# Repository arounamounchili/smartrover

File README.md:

# SmartRover

SmartRover is a teleoperated 4WD mobile robot built on the **ESP32-S3** in `no_std` asynchronous Rust (`embassy` + `esp-hal`). The repository includes the firmware, an embedded single-file web cockpit, KiCad PCB/manufacturing files, and parametric `build123d` mechanical models.

## Overview

- **Drive & Camera:** Differential 4WD skid-steer (4× A3908EEETR-T H-bridges on `MCPWM0` in paired left/right banks, no wheel encoders) + SPI Arducam OV5642 MJPEG stream on Core 1.
- **Browser Teleoperation:** Web Gamepad API (PlayStation, Xbox, and standard controllers), `WASD`/arrow keys, and touch/mouse X/Y pad.
- **Onboard Safety Supervision:**
  - **Obstacle Assist (VL53L0X):** 3-sample median-filtered ranging scales forward throttle below 320 mm, latches forward stop at <= 140 mm (165 mm release hysteresis; reverse and pivot steering remain allowed), and filters invalid or weak signal returns to ignore grazing floor reflections.
  - **Tilt & Free-Fall (BMI323):** Latches motor cutoff past 0.68 g for 400 ms or on free-fall; recovers once upright with neutral sticks.
  - **Watchdog & Battery (`ADC1`):** Cuts drive output after 600 ms without a control packet or below 15% battery (20% hysteresis).

## Project Structure

- [`src/`](src/) — ESP32-S3 firmware (`domain/` control & safety logic, `adapters/` tasks & shared state, `drivers/` for MCPWM0, BMI323, VL53L0X, OV5642, and ADC1, `camera/` Core 1 capture, `network/` Wi-Fi/DHCP/HTTP/MJPEG server).
- [`dashboard/`](dashboard/) — Single-file web cockpit (`dashboard.html.gz`) embedded into firmware flash.
- [`hardware/`](hardware/) — KiCad schematics, 4-layer PCB (45 × 80 mm), and [`hardware/manufacturing/`](hardware/manufacturing/) fabrication files (BOM, Gerbers, pick-and-place).
- [`mechanical/`](mechanical/) & [`3d-printing/`](3d-printing/) — Parametric `build123d` CAD sources and support-free printable STEP/STL files (62.0 × 115.5 mm unibody chassis).

## Controls

| Function | Gamepad | Keyboard | Touch / Mouse |
| :--- | :--- | :--- | :--- |
| **Throttle** | Left Stick Y or R2 / L2 Triggers | `W` / `S` or `Up` / `Down` | Drag pad vertically |
| **Steering** | Left Stick X or Right Stick X | `A` / `D` or `Left` / `Right` | Drag pad horizontally |
| **Speed Gear** | `LB` / `RB` (`L1` / `R1`) | `1`, `2`, `3` | Click Crawl / Normal / Sport |
| **Brake** | `B` (Circle) | `Space` | Hold Brake button |
| **Obstacle Assist** | `Y` (Triangle) | — | Click Assist button |

## Pinout (ESP32-S3-MINI-1)

| Subsystem | GPIO | Peripheral | Notes |
| :--- | :---: | :---: | :--- |
| **I2C Bus** | `8` (SDA), `9` (SCL) | `I2C0` | 400 kHz (BMI323, VL53L0X, OV5642) |
| **Camera SPI** | `34` (CS), `35` (MOSI), `36` (SCK), `37` (MISO) | `SPI2` | 8 MHz FIFO burst read on Core 1 |
| **Motors** | `11`, `12` (Left), `13`, `14` (Right) | `MCPWM0` | 16 kHz PWM to A3908 H-bridges |
| **Battery Sense** | `1` | `ADC1` | 2:1 voltage divider (3.3 V to 4.2 V) |
| **Status LEDs** | `3`, `4`, `5`, `6` | `GPIO` | Front White (`3`, `4`), Rear Red (`5`, `6`) state, ADAS, and fault indicators |

## Building and Testing

### Prerequisites
- **Rust (`esp` toolchain):** `channel = "esp"` ([`rust-toolchain.toml`](rust-toolchain.toml)) targeting `xtensa-esp32s3-none-elf` via `espup`, plus `espflash`.
- **Node.js & npm:** For `dashboard/` tests and asset bundling (`dashboard/dashboard.html.gz`).
- **`uv` *(optional, CAD only)*:** For verifying or regenerating 3D models in [`mechanical/`](mechanical/README.md).

### Test, Build & CAD Commands

```bash
# Run Rust host unit tests + dashboard unit tests (no ESP32-S3 required)
make test

# Run the full local CI suite (fmt, tests, dashboard bundle check, clippy, ESP32-S3 builds)
make ci

# Rebuild dashboard/dashboard.html.gz after editing dashboard/ (or `cd dashboard && npm run dev`)
make dashboard

# Verify clearances & regenerate STLs/STEPs in 3d-printing/
make cad-verify && make cad-export
```

### Flash to ESP32-S3

Connect a 3.3 V USB-UART bridge to `J201` (onboard USB-C is power-only), switch battery power **ON**, and enter download mode (**hold `BOOT`, press `RESET`, release `BOOT`**):

```bash
# Default SoftAP mode (SmartRover_AP / smartrover123 -> http://192.168.4.1/)
make dashboard && make flash PORT=/dev/cu.usbserial-0001

# Station (STA) mode (joins 2.4 GHz Wi-Fi; compile-time when WIFI_SSID is set)
make flash-sta WIFI_SSID="Your_2.4GHz_SSID" WIFI_PASS="Your_Password" PORT=/dev/cu.usbserial-0001
```

- **Port & baud overrides:** Omit `PORT=...` to auto-select, or override defaults (`--before no-reset -B 115200`) with `FLASH_BEFORE=default-reset BAUD=460800`.
- **Wi-Fi mode:** Selected at compile time via `WIFI_SSID`. In STA mode, the rover retries every 5 s without falling back to SoftAP and prints its assigned cockpit URL on serial (`Rover Cockpit: http://<ip>/`).

See [`mechanical/README.md`](mechanical/README.md) and [`3d-printing/README.md`](3d-printing/README.md) for CAD and printing details.

## HTTP API

| Endpoint | Description |
| :--- | :--- |
| `GET /` | Serves the gzip-compressed web cockpit (`dashboard.html.gz`). |
| `POST /control?t=&s=&g=&b=&a=` | Updates throttle/steering (`-1000..=1000`), gear (`1..=3`), brake (`0`/`1`), and obstacle assist (`0`/`1`); returns status JSON. |
| `GET /status` | Returns telemetry JSON (`dist`, `batt`, `state`, `adas_active`, `left_pwm`, `right_pwm`, `rssi`, `tof_ok`, `imu_ok`). |
| `GET /stream` | Multipart MJPEG camera stream (`multipart/x-mixed-replace; boundary=frame`; single active viewer, new connections preempt older ones). |

## License

MIT License. See [LICENSE](LICENSE).

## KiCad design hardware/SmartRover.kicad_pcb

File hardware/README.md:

# SmartRover Hardware & PCB

4-layer 1.6 mm FR4 carrier board (45 × 80 mm) designed in **KiCad 9.0+**.

- **Schematics (PDF):** [`schematics.pdf`](schematics.pdf)
- **KiCad Project:** [`SmartRover.kicad_pro`](SmartRover.kicad_pro), [`SmartRover.kicad_pcb`](SmartRover.kicad_pcb), and [`SmartRover.kicad_sch`](SmartRover.kicad_sch) linking:
  - [`PowerSupply.kicad_sch`](PowerSupply.kicad_sch) — MCP73833 LiPo charger (`IC101`), MP2153 3.3 V buck (`IC102`), USB-C power input (`J101`), JST-PH battery (`J102`), SPDT charge/run switch (`S101`).
  - [`Microcontroller.kicad_sch`](Microcontroller.kicad_sch) — ESP32-S3-MINI-1-N8 (`U201`), UART header (`J201`), Tag-Connect JTAG (`J202`), RESET/BOOT buttons (`S201`/`S202`), status LEDs.
  - [`SensorActuator.kicad_sch`](SensorActuator.kicad_sch) — 4× A3908 motor drivers (`IC301–IC304`), BMI323 IMU (`IC305`), Arducam header (`J309`), JST-SH I2C/ToF header (`J310`).
- **Manufacturing:** [`manufacturing/`](manufacturing/) (`BOM.csv`, `Gerbers.zip`, `Position-file.csv`).

All symbols and footprints are embedded inside the schematic and PCB files, so you can inspect the design and re-export fabrication outputs in KiCad 9.0+ without external libraries. (Custom third-party libraries referenced in [`sym-lib-table`](sym-lib-table) / [`fp-lib-table`](fp-lib-table) are only needed if you update symbols/footprints from libraries.)

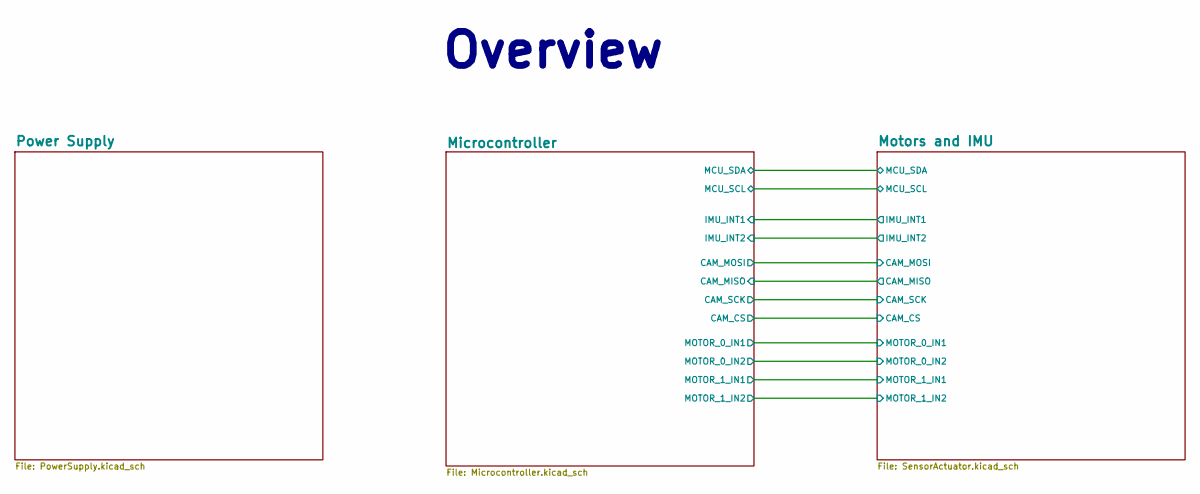
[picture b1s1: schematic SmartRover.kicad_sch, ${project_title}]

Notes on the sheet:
Overview

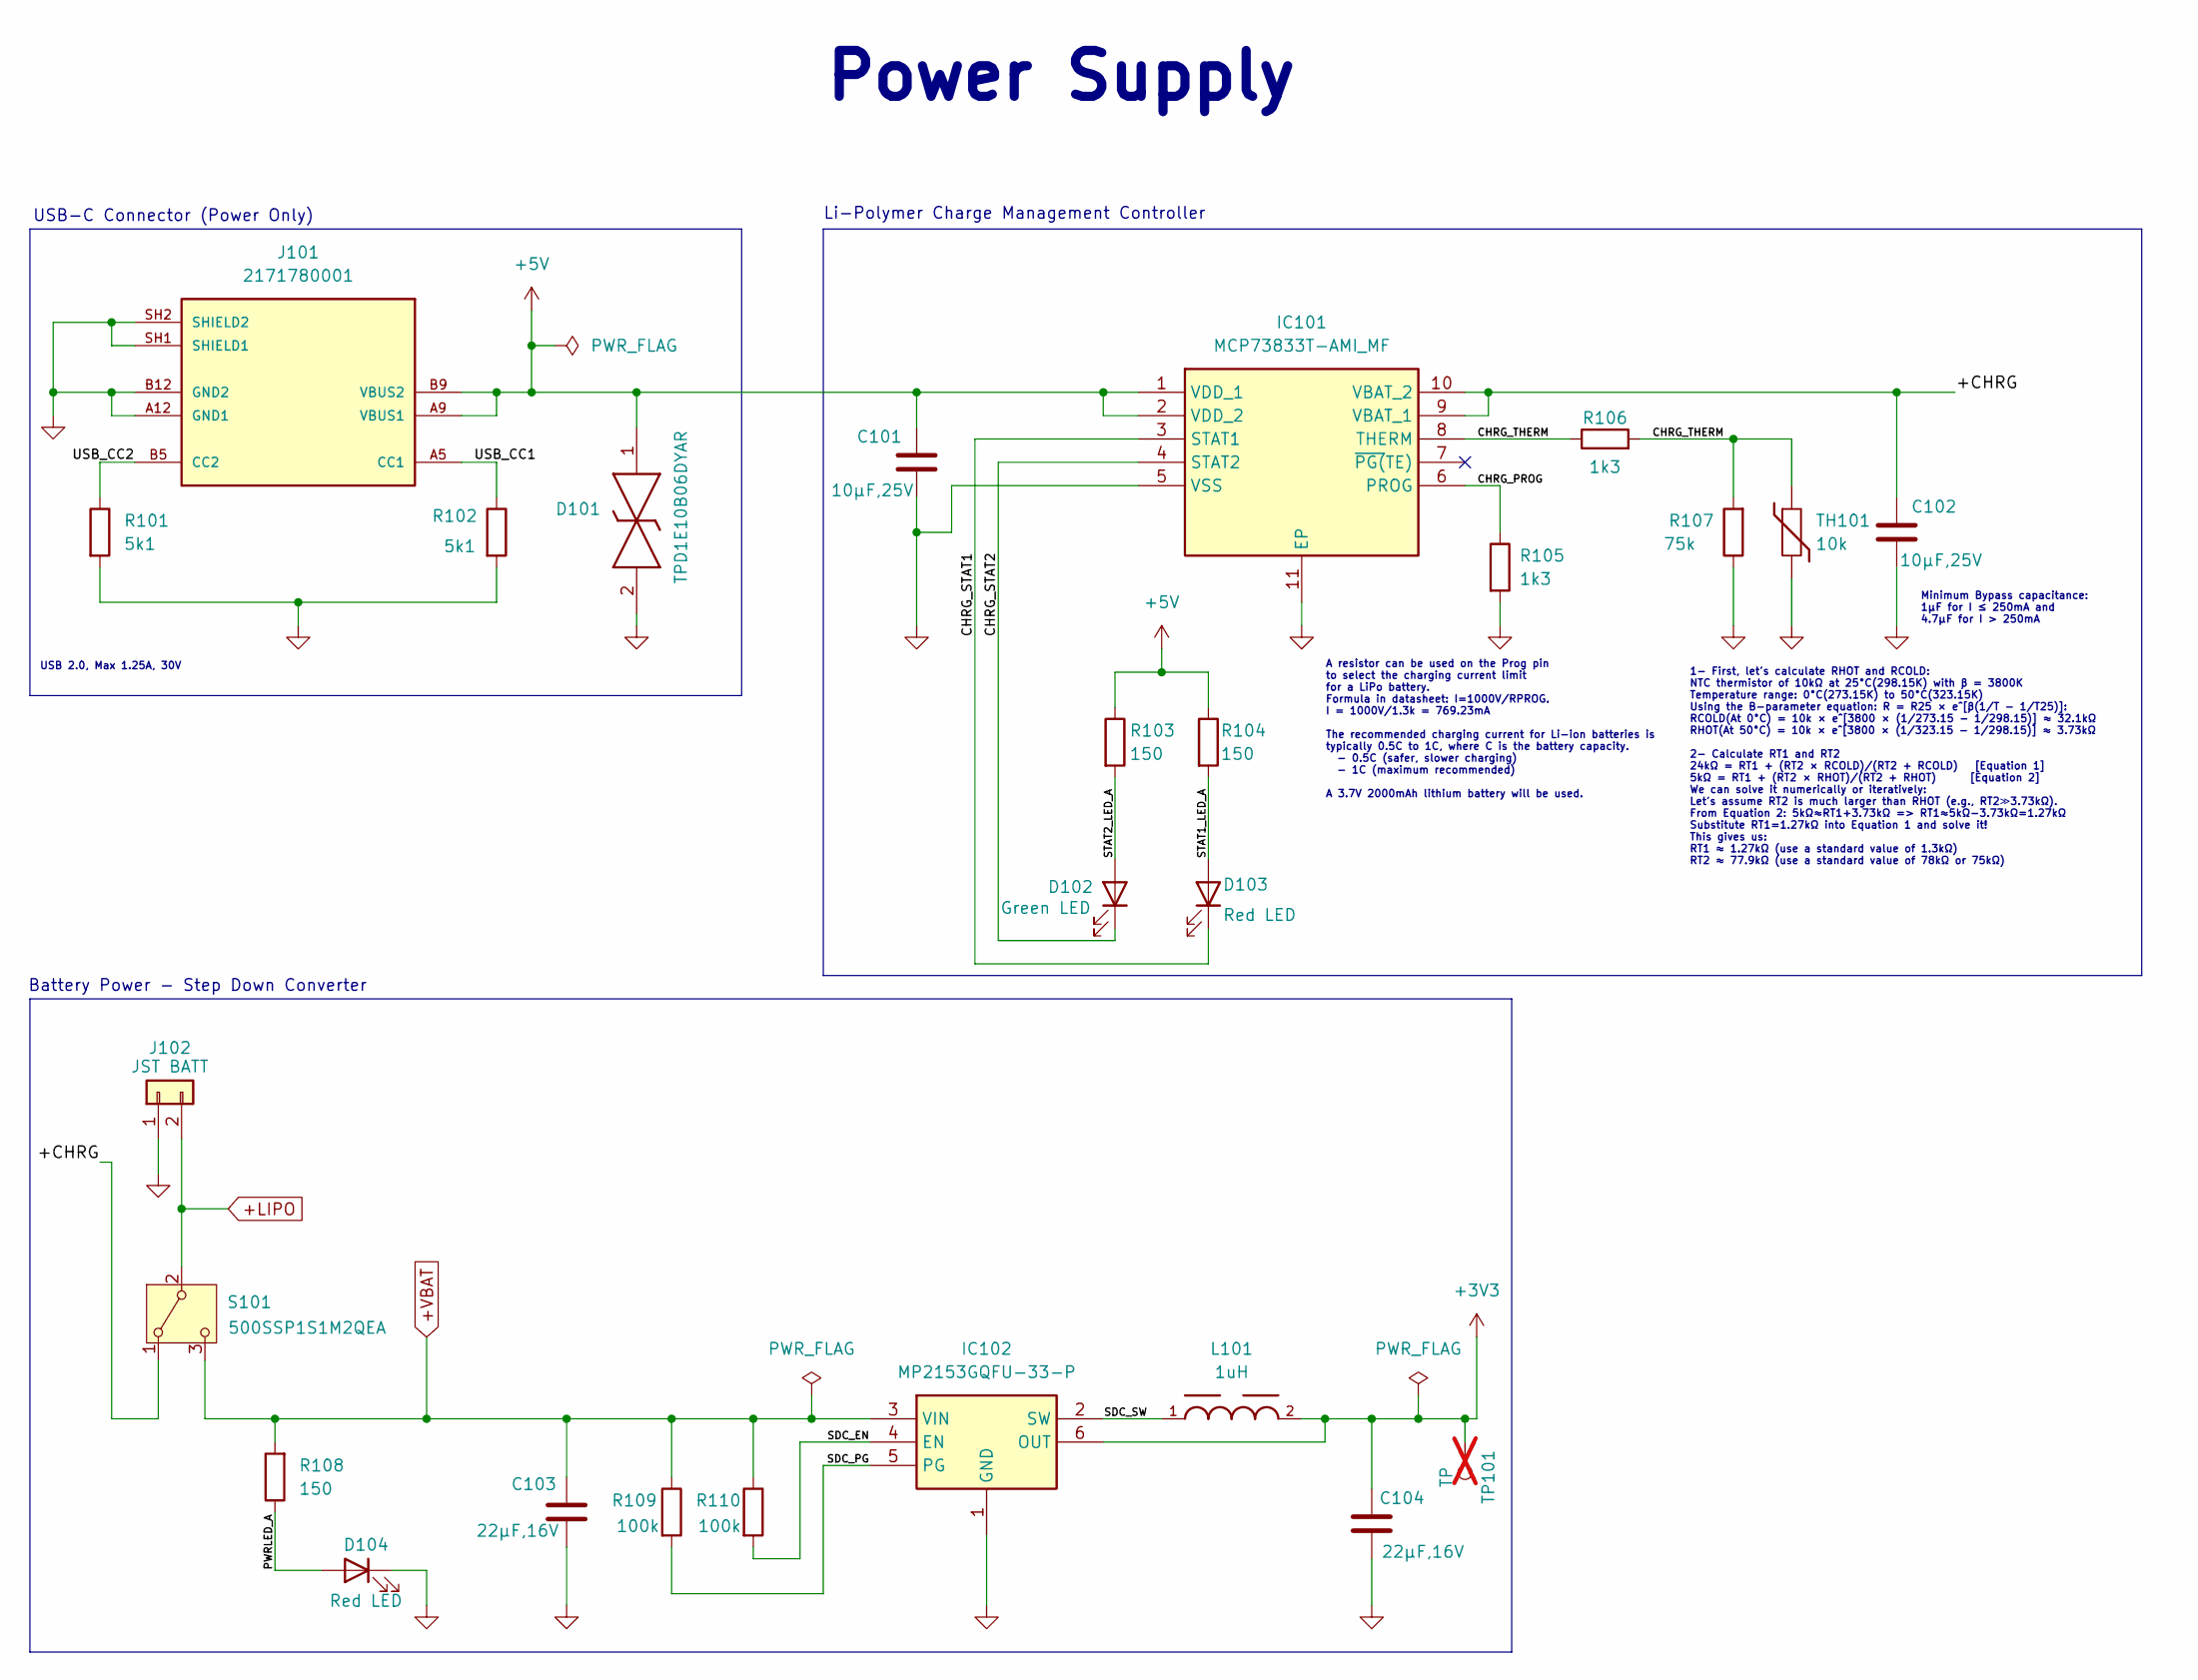
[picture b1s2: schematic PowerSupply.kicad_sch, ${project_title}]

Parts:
C101, C102: 10µF,25V; C_0603_1608Metric; Manufacturer Part Number CL10A106MA8NRNC; JLCPCB Part Number C96446
C103, C104: 22µF,16V; C_0603_1608Metric; Manufacturer Part Number CL10A226MO7JZNC; JLCPCB Part Number C2762594
D101: TPD1E10B06DYAR; SODFL1608X77N; Mouser Part Number 595-TPD1E10B06DYAR
D102: Green LED; LED_0603_1608Metric; Manufacturer Part Number 150060GS75000; JLCPCB Part Number C5252984
D103, D104: Red LED; LED_0603_1608Metric; Manufacturer Part Number 150060RS75000; JLCPCB Part Number C3030991
IC101: MCP73833T-AMI_MF; SON50P300X300X100-11N-D; Mouser Part Number 579-MCP73833T-AMI/MF
IC102: MP2153GQFU-33-P; Manufacturer Part Number MP2153GQFU-33-P; JLCPCB Part Number C6992808
J101: 2171780001; MOLEX_2171780001; PARTREV A1; JLCPCB Part Number C3197609
J102: JST BATT; JST_B2B-PH-K-S; Manufacturer Part Number B2B-PH-K-S; JLCPCB Part Number C20504437
L101: 1uH; WE-LHMI_4020; Manufacturer Part Number 74437324010; JLCPCB Part Number C2045726
R101, R102: 5k1; R_0603_1608Metric; Manufacturer Part Number ERJ-3EKF5101V; JLCPCB Part Number C123727
R103, R104, R108: 150; R_0603_1608Metric; Manufacturer Part Number RC0603FR-07150RL; JLCPCB Part Number C114608
R105, R106: 1k3; R_0603_1608Metric; Manufacturer Part Number ERA-3AEB132V; JLCPCB Part Number C543641
R107: 75k; R_0603_1608Metric; Manufacturer Part Number ERJ-PB3B7502V; JLCPCB Part Number C413688
R109, R110: 100k; R_0603_1608Metric; Manufacturer Part Number ERJ-3EKF1003V; JLCPCB Part Number C189597
S101: 500SSP1S1M2QEA; Manufacturer Part Number 500SSP1S1M2QEA; JLCPCB Part Number C6689030
TH101: 10k; R_0603_1608Metric; Manufacturer Part Number NTCG163JF103HT1; JLCPCB Part Number C531304
TP101: TP; TestPoint_Pad_D1.0mm; not fitted

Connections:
+3V3: C104.1, IC102.6 (OUT), L101.2, TP101.1; also elsewhere on the board
+5V: C101.1, D101.1, IC101.1 (VDD_1), IC101.2 (VDD_2), J101.A9 (VBUS1), J101.B9 (VBUS2), R103.1, R104.1
+LIPO: J102.2, S101.2 (B); also elsewhere on the board
+VBAT: C103.1, IC102.3 (VIN), R108.2, R109.1, R110.1, S101.3 (C); also elsewhere on the board
/Power Supply/+CHRG: C102.1, IC101.9 (VBAT_1), IC101.10 (VBAT_2), S101.1 (A)
/Power Supply/CHRG_PROG: IC101.6 (PROG), R105.1
/Power Supply/CHRG_STAT1: D103.1 (K), IC101.3 (STAT1)
/Power Supply/CHRG_STAT2: D102.1 (K), IC101.4 (STAT2)
/Power Supply/CHRG_THERM: IC101.8 (THERM), R106.1, R106.2, R107.2, TH101.1
/Power Supply/PWRLED_A: D104.2 (A), R108.1
/Power Supply/SDC_EN: IC102.4 (EN), R110.2
/Power Supply/SDC_PG: IC102.5 (PG), R109.2
/Power Supply/SDC_SW: IC102.2 (SW), L101.1
/Power Supply/STAT1_LED_A: D103.2 (A), R104.2
/Power Supply/STAT2_LED_A: D102.2 (A), R103.2
/Power Supply/USB_CC1: J101.A5 (CC1), R102.1
/Power Supply/USB_CC2: J101.B5 (CC2), R101.1
GND: C101.2, C102.2, C103.2, C104.2, D101.2, D104.1 (K), IC101.5 (VSS), IC101.11 (EP), IC102.1 (GND), J101.A12 (GND1), J101.B12 (GND2), J101.SH1 (SHIELD1), J101.SH2 (SHIELD2), J102.1, R101.2, R102.2, R105.2, R107.1, TH101.2; also elsewhere on the board

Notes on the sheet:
USB 2.0, Max 1.25A, 30V
Battery Power - Step Down Converter
A resistor can be used on the Prog pin to select the charging current limit for a LiPo battery. Formula in datasheet: I=1000V/RPROG. I = 1000V/1.3k = 769.23mA The recommended charging current for Li-ion batteries is typically 0.5C to 1C, where C is the battery capacity. - 0.5C (safer, slower chargi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
Power Supply
Minimum Bypass capacitance: 1µF for I ≤ 250mA and 4.7µF for I > 250mA
USB-C Connector (Power Only)
Li-Polymer Charge Management Controller
1- First, let's calculate RHOT and RCOLD: NTC thermistor of 10kΩ at 25°C(298.15K) with β = 3800K Temperature range: 0°C(273.15K) to 50°C(323.15K) Using the B-parameter equation: R = R25 × e^[β(1/T - 1/T25)]: RCOLD(At 0°C) = 10k × e^[3800 × (1/273.15 - 1/298.15)] ≈ 32.1kΩ RHOT(At 50°C) = 10k × e^[38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

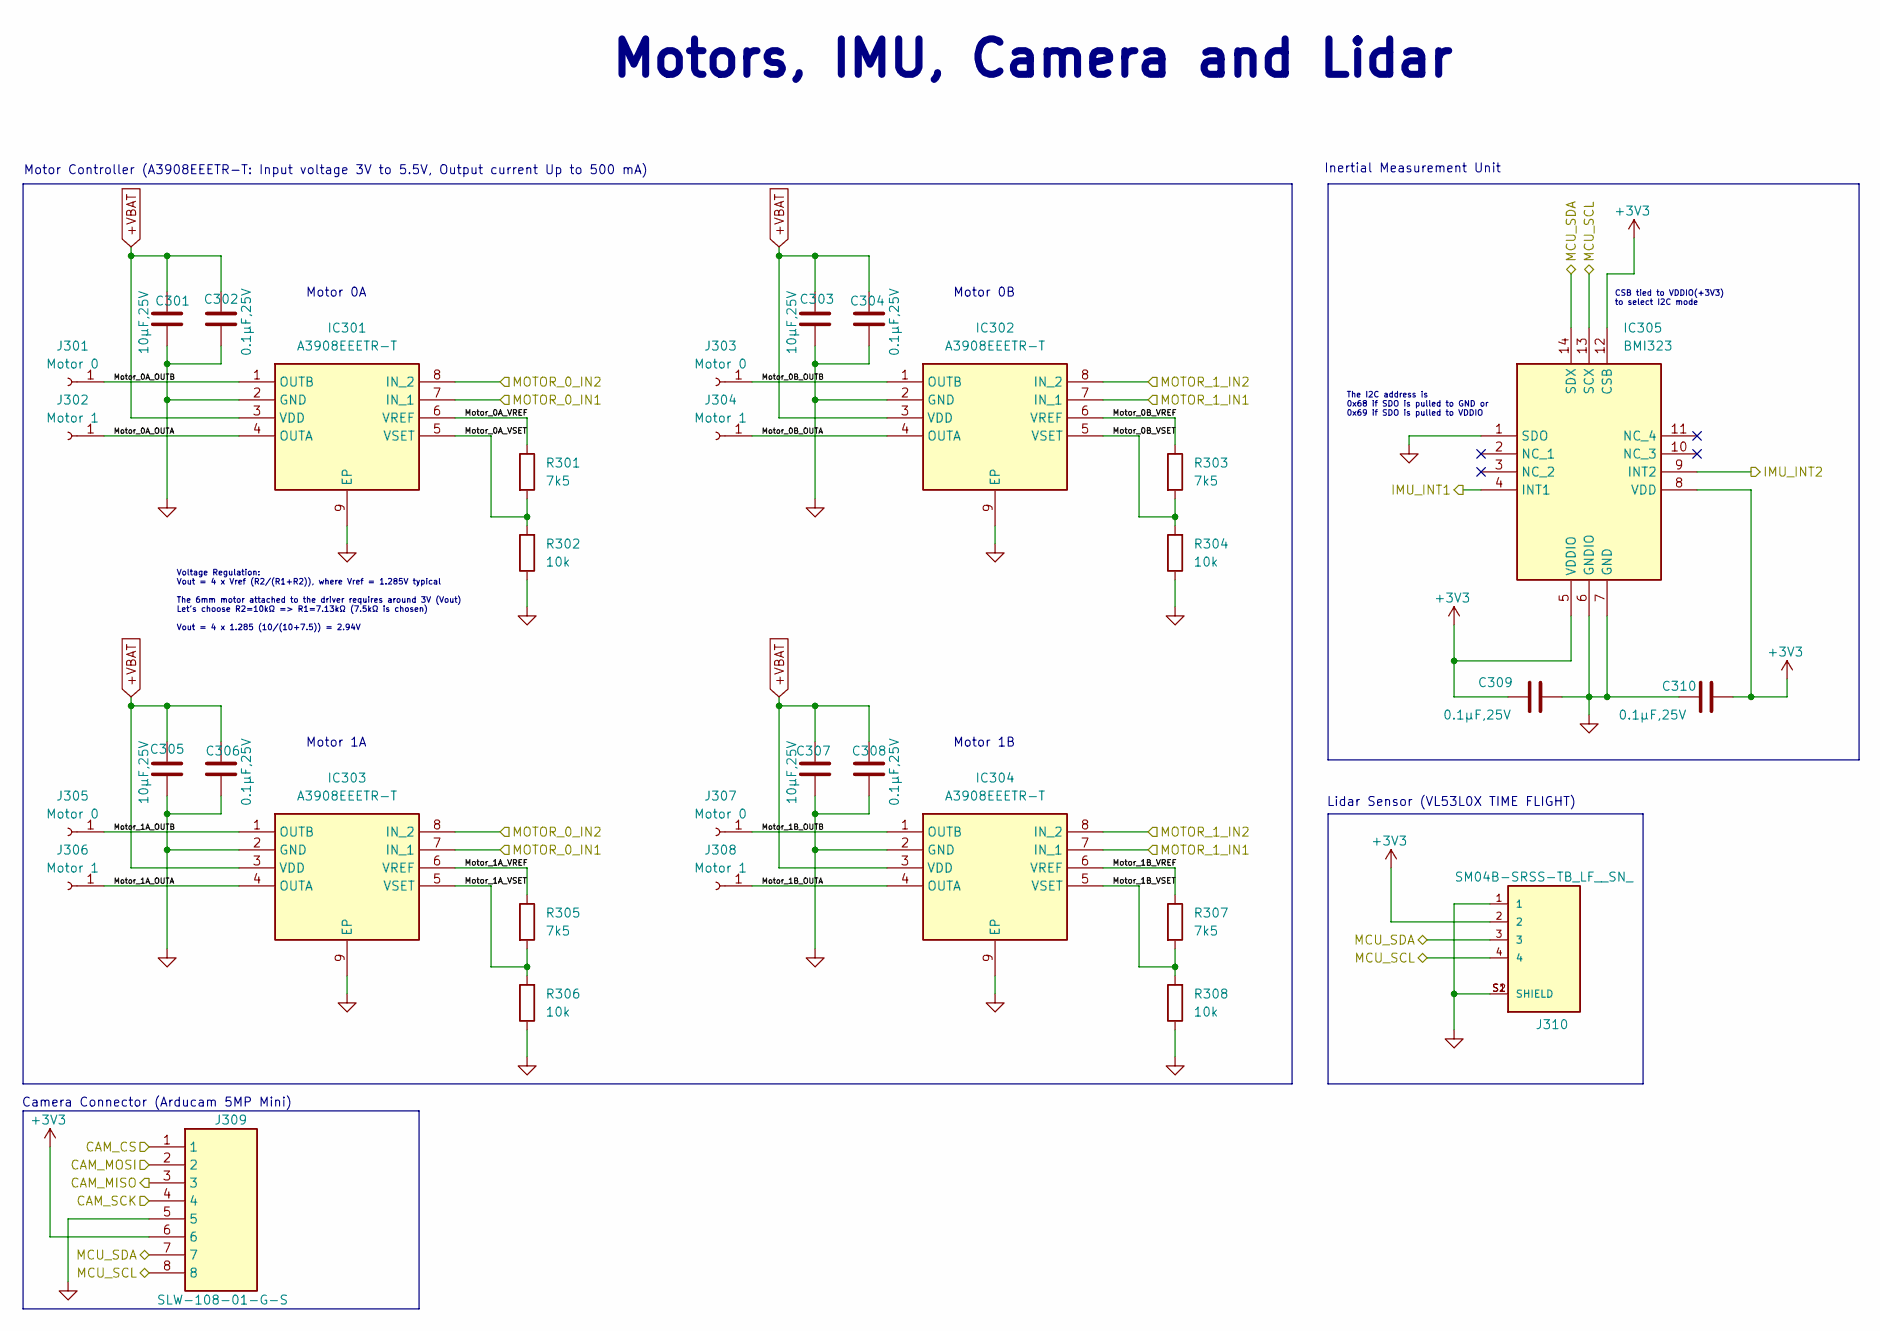
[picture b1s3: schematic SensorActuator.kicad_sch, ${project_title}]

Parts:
C301, C303, C305, C307: 10µF,25V; C_0603_1608Metric; Manufacturer Part Number CL10A106MA8NRNC; JLCPCB Part Number C96446
C302, C304, C306, C308, C309, C310: 0.1µF,25V; C_0603_1608Metric; Manufacturer Part Number CL10B104KA8WPNC; JLCPCB Part Number C346190
IC301, IC302, IC303, IC304: A3908EEETR-T; SON50P200X200X60-9N-D; Mouser Part Number 250-A3908EEETR-T
IC305: BMI323; Mouser Part Number 262-BMI323
J301, J303, J305, J307: Motor 0; TestPoint_Pad_2.0x2.0mm
J302, J304, J306, J308: Motor 1; TestPoint_Pad_2.0x2.0mm
J309: SLW-108-01-G-S; Mouser Part Number 200-SLW10801GS
J310: SM04B-SRSS-TB_LF__SN_; JST_SM04B-SRSS-TB_LF__SN_; Manufacturer Part Number SM04B-SRSS-TB(LF)(SN); JLCPCB Part Number C160404
R301, R303, R305, R307: 7k5; R_0603_1608Metric; Manufacturer Part Number AT0603BRD077K5L; JLCPCB Part Number C855966
R302, R304, R306, R308: 10k; R_0603_1608Metric; Manufacturer Part Number RC1608F103CS; JLCPCB Part Number C17441167

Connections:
+3V3: C309.1, C310.1, IC305.5 (VDDIO), IC305.8 (VDD), IC305.12 (CSB), J309.6, J310.2; also elsewhere on the board
+VBAT: C301.1, C302.1, C303.1, C304.1, C305.1, C306.1, C307.1, C308.1, IC301.3 (VDD), IC302.3 (VDD), IC303.3 (VDD), IC304.3 (VDD); also elsewhere on the board
/Microcontroller/CAM_CS: J309.1; also elsewhere on the board
/Microcontroller/CAM_MISO: J309.3; also elsewhere on the board
/Microcontroller/CAM_MOSI: J309.2; also elsewhere on the board
/Microcontroller/CAM_SCK: J309.4; also elsewhere on the board
/Microcontroller/IMU_INT1: IC305.4 (INT1); also elsewhere on the board
/Microcontroller/IMU_INT2: IC305.9 (INT2); also elsewhere on the board
/Microcontroller/MCU_SCL: IC305.13 (SCX), J309.8, J310.4; also elsewhere on the board
/Microcontroller/MCU_SDA: IC305.14 (SDX), J309.7, J310.3; also elsewhere on the board
/Microcontroller/MOTOR_0_IN1: IC301.7 (IN_1), IC303.7 (IN_1); also elsewhere on the board
/Microcontroller/MOTOR_0_IN2: IC301.8 (IN_2), IC303.8 (IN_2); also elsewhere on the board
/Microcontroller/MOTOR_1_IN1: IC302.7 (IN_1), IC304.7 (IN_1); also elsewhere on the board
/Microcontroller/MOTOR_1_IN2: IC302.8 (IN_2), IC304.8 (IN_2); also elsewhere on the board
/Motors and IMU/Motor_0A_OUTA: IC301.4 (OUTA), J302.1
/Motors and IMU/Motor_0A_OUTB: IC301.1 (OUTB), J301.1
/Motors and IMU/Motor_0A_VREF: IC301.6 (VREF), R301.1
/Motors and IMU/Motor_0A_VSET: IC301.5 (VSET), R301.2, R302.2
/Motors and IMU/Motor_0B_OUTA: IC302.4 (OUTA), J304.1
/Motors and IMU/Motor_0B_OUTB: IC302.1 (OUTB), J303.1
/Motors and IMU/Motor_0B_VREF: IC302.6 (VREF), R303.1
/Motors and IMU/Motor_0B_VSET: IC302.5 (VSET), R303.2, R304.2
/Motors and IMU/Motor_1A_OUTA: IC303.4 (OUTA), J306.1
/Motors and IMU/Motor_1A_OUTB: IC303.1 (OUTB), J305.1
/Motors and IMU/Motor_1A_VREF: IC303.6 (VREF), R305.1
/Motors and IMU/Motor_1A_VSET: IC303.5 (VSET), R305.2, R306.2
/Motors and IMU/Motor_1B_OUTA: IC304.4 (OUTA), J308.1
/Motors and IMU/Motor_1B_OUTB: IC304.1 (OUTB), J307.1
/Motors and IMU/Motor_1B_VREF: IC304.6 (VREF), R307.1
/Motors and IMU/Motor_1B_VSET: IC304.5 (VSET), R307.2, R308.2
GND: C301.2, C302.2, C303.2, C304.2, C305.2, C306.2, C307.2, C308.2, C309.2, C310.2, IC301.2 (GND), IC301.9 (EP), IC302.2 (GND), IC302.9 (EP), IC303.2 (GND), IC303.9 (EP), IC304.2 (GND), IC304.9 (EP), IC305.1 (SDO), IC305.6 (GNDIO), IC305.7 (GND), J309.5, J310.1, J310.S1 (SHIELD), J310.S2 (SHIELD), R302.1, R304.1, R306.1, R308.1; also elsewhere on the board

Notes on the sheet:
The I2C address is 0x68 if SDO is pulled to GND or 0x69 if SDO is pulled to VDDIO
Inertial Measurement Unit
Motors, IMU, Camera and Lidar
CSB tied to VDDIO(+3V3) to select I2C mode
Camera Connector (Arducam 5MP Mini)
Voltage Regulation: Vout = 4 x Vref (R2/(R1+R2)), where Vref = 1.285V typical The 6mm motor attached to the driver requires around 3V (Vout) Let's choose R2=10kΩ => R1=7.13kΩ (7.5kΩ is chosen) Vout = 4 x 1.285 (10/(10+7.5)) = 2.94V
Motor 0A
Motor 1A
Motor 0B
Motor Controller (A3908EEETR-T: Input voltage 3V to 5.5V, Output current Up to 500 mA)
Motor 1B
Lidar Sensor (VL53L0X TIME FLIGHT)

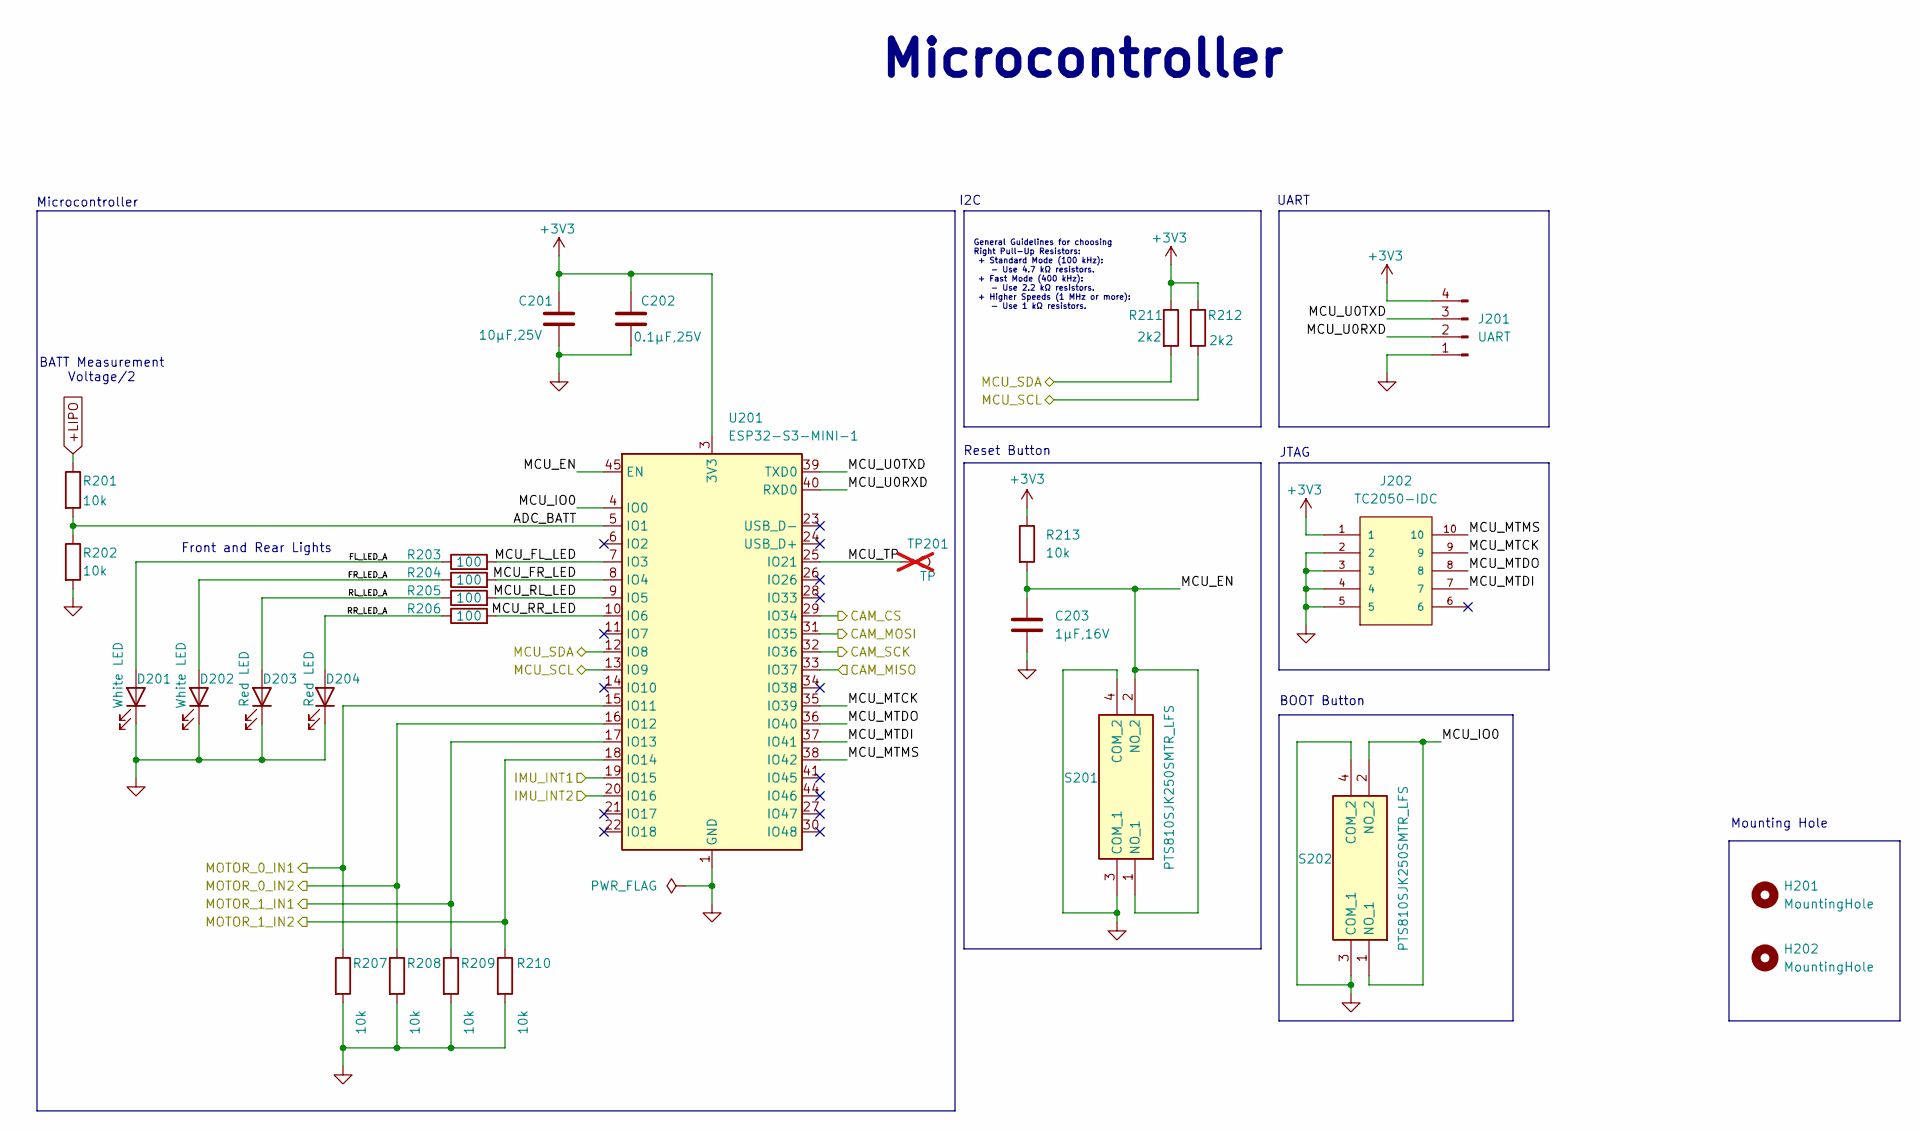
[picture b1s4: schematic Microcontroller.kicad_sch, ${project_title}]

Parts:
C201: 10µF,25V; C_0603_1608Metric; Manufacturer Part Number CL10A106MA8NRNC; JLCPCB Part Number C96446
C202: 0.1µF,25V; C_0603_1608Metric; Manufacturer Part Number CL10B104KA8WPNC; JLCPCB Part Number C346190
C203: 1µF,16V; C_0603_1608Metric; Manufacturer Part Number CL10B105KO8VPNC; JLCPCB Part Number C346194
D201, D202: White LED; LED_0603_1608Metric; Manufacturer Part Number IN-S63AT5UW; JLCPCB Part Number C7207730
D203, D204: Red LED; LED_0603_1608Metric; Manufacturer Part Number 150060RS75000; JLCPCB Part Number C3030991
H201, H202: MountingHole; MountingHole_2.7mm_M2.5
J201: UART; PinHeader_1x04_P2.54mm_Vertical; Manufacturer Part Number 61300411121; JLCPCB Part Number C5184785
J202: TC2050-IDC; TAG-CONNECT_TC2050-IDC; PARTREV A; DigiKey_Part_Number TC2050-IDC-ND
R201, R202, R207, R208, R209, R210, R213: 10k; R_0603_1608Metric; Manufacturer Part Number RC1608F103CS; JLCPCB Part Number C17441167
R203, R204, R205, R206: 100; R_0603_1608Metric; Manufacturer Part Number RC0603FR-07100RL; JLCPCB Part Number C105588
R211, R212: 2k2; R_0603_1608Metric; Manufacturer Part Number RC1608F222CS; JLCPCB Part Number C3984455
S201, S202: PTS810SJK250SMTR_LFS; PTS810SJK250SMTRLFS; Mouser Part Number 611-PTS810SJK250SMTR
TP201: TP; TestPoint_Pad_D1.0mm; not fitted
U201: ESP32-S3-MINI-1; ESP32-S2-MINI-1; Manufacturer Part Number ESP32-S3-MINI-1-N8; JLCPCB Part Number C2913206

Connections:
+3V3: C201.1, C202.1, J201.4, J202.1, R211.1, R212.1, R213.1, U201.3 (3V3); also elsewhere on the board
+LIPO: R201.1; also elsewhere on the board
/Microcontroller/ADC_BATT: R201.2, R202.1, U201.5 (IO1)
/Microcontroller/CAM_CS: U201.29 (IO34); also elsewhere on the board
/Microcontroller/CAM_MISO: U201.33 (IO37); also elsewhere on the board
/Microcontroller/CAM_MOSI: U201.31 (IO35); also elsewhere on the board
/Microcontroller/CAM_SCK: U201.32 (IO36); also elsewhere on the board
/Microcontroller/FL_LED_A: D201.2 (A), R203.1
/Microcontroller/FR_LED_A: D202.2 (A), R204.1
/Microcontroller/IMU_INT1: U201.19 (IO15); also elsewhere on the board
/Microcontroller/IMU_INT2: U201.20 (IO16); also elsewhere on the board
/Microcontroller/MCU_EN: C203.1, R213.2, S201.1 (NO_1), S201.2 (NO_2), U201.45 (EN)
/Microcontroller/MCU_FL_LED: R203.2, U201.7 (IO3)
/Microcontroller/MCU_FR_LED: R204.2, U201.8 (IO4)
/Microcontroller/MCU_IO0: S202.1 (NO_1), S202.2 (NO_2), U201.4 (IO0)
/Microcontroller/MCU_MTCK: J202.9, U201.35 (IO39)
/Microcontroller/MCU_MTDI: J202.7, U201.37 (IO41)
/Microcontroller/MCU_MTDO: J202.8, U201.36 (IO40)
/Microcontroller/MCU_MTMS: J202.10, U201.38 (IO42)
/Microcontroller/MCU_RL_LED: R205.2, U201.9 (IO5)
/Microcontroller/MCU_RR_LED: R206.2, U201.10 (IO6)
/Microcontroller/MCU_SCL: R212.2, U201.13 (IO9); also elsewhere on the board
/Microcontroller/MCU_SDA: R211.2, U201.12 (IO8); also elsewhere on the board
/Microcontroller/MCU_TP: TP201.1, U201.25 (IO21)
/Microcontroller/MCU_U0RXD: J201.2, U201.40 (RXD0)
/Microcontroller/MCU_U0TXD: J201.3, U201.39 (TXD0)
/Microcontroller/MOTOR_0_IN1: R207.1, U201.15 (IO11); also elsewhere on the board
/Microcontroller/MOTOR_0_IN2: R208.1, U201.16 (IO12); also elsewhere on the board
/Microcontroller/MOTOR_1_IN1: R209.1, U201.17 (IO13); also elsewhere on the board
/Microcontroller/MOTOR_1_IN2: R210.1, U201.18 (IO14); also elsewhere on the board
/Microcontroller/RL_LED_A: D203.2 (A), R205.1
/Microcontroller/RR_LED_A: D204.2 (A), R206.1
GND: C201.2, C202.2, C203.2, D201.1 (K), D202.1 (K), D203.1 (K), D204.1 (K), J201.1, J202.2, J202.3, J202.4, J202.5, R202.2, R207.2, R208.2, R209.2, R210.2, S201.3 (COM_1), S201.4 (COM_2), S202.3 (COM_1), S202.4 (COM_2), U201.1 (GND), U201.2 (GND), U201.42 (GND), U201.43 (GND), U201.46 (GND), U201.47 (GND), U201.48 (GND), U201.49 (GND), U201.50 (GND), U201.51 (GND), U201.52 (GND), U201.53 (GND), U201.54 (GND), U201.55 (GND), U201.56 (GND), U201.57 (GND), U201.58 (GND), U201.59 (GND), U201.60 (GND), U201.61 (GND), U201.62 (GND), U201.63 (GND), U201.64 (GND), U201.65 (GND); also elsewhere on the board

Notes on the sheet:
I2C
UART
Reset Button
BOOT Button
Microcontroller
JTAG
Mounting Hole
BATT Measurement Voltage/2
General Guidelines for choosing Right Pull-Up Resistors: + Standard Mode (100 kHz): - Use 4.7 kΩ resistors. + Fast Mode (400 kHz): - Use 2.2 kΩ resistors. + Higher Speeds (1 MHz or more): - Use 1 kΩ resistors.
Front and Rear Lights

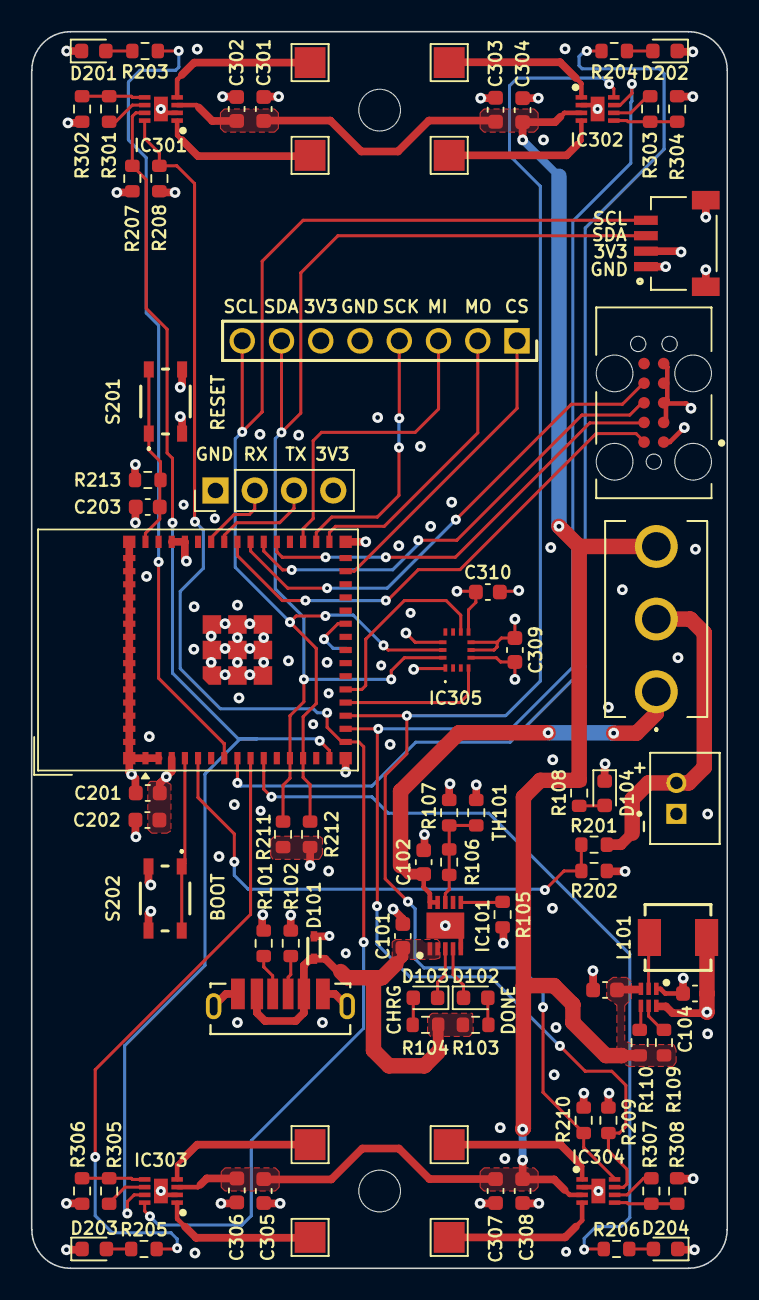
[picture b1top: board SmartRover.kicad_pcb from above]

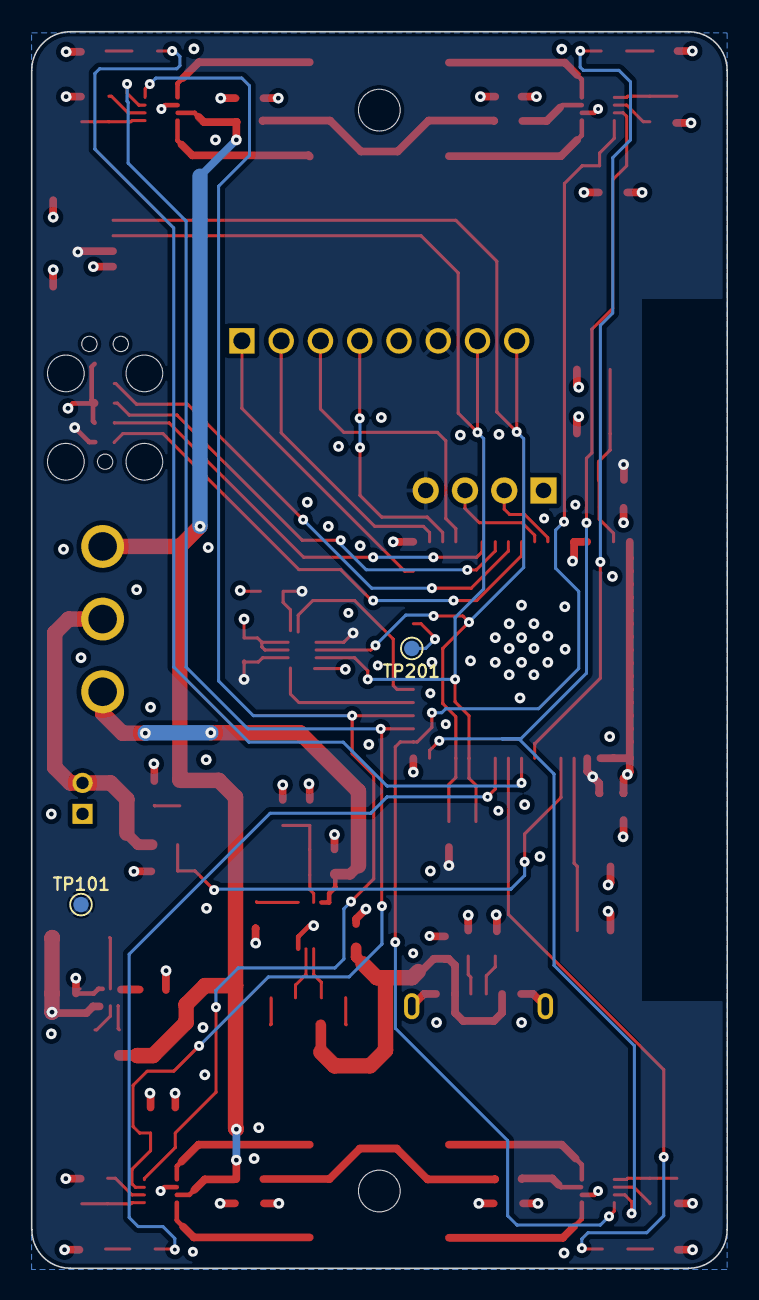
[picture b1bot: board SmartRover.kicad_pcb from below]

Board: 4 copper layers, 45.0 x 80.0 mm, 87 parts (2 on the bottom side), 64 nets.

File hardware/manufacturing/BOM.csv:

"Reference","Value","Footprint","Qty","Manufacturer Part Number","Manufacturer"
"C101,C102,C201,C301,C303,C305,C307","10µF,25V","Capacitor_SMD:C_0603_1608Metric","7","CL10A106MA8NRNC","Samsung Electro-Mechanics"
"C103,C104","22µF,16V","Capacitor_SMD:C_0603_1608Metric","2","CL10A226MO7JZNC","Samsung Electro-Mechanics"
"C202,C302,C304,C306,C308,C309,C310","0.1µF,25V","Capacitor_SMD:C_0603_1608Metric","7","CL10B104KA8WPNC","Samsung Electro-Mechanics"
"C203","1µF,16V","Capacitor_SMD:C_0603_1608Metric","1","CL10B105KO8VPNC","Samsung Electro-Mechanics"
"D101","TPD1E10B06DYAR","TPD1E10B06DYAR:SODFL1608X77N","1","TPD1E10B06DYAR","Texas Instruments"
"D102","Green LED","LED_SMD:LED_0603_1608Metric","1","150060GS75000","Würth Elektronik"
"D103,D104,D203,D204","Red LED","LED_SMD:LED_0603_1608Metric","4","150060RS75000","Würth Elektronik"
"D201,D202","White LED","LED_SMD:LED_0603_1608Metric","2","IN-S63AT5UW","Inolux"
"IC101","MCP73833T-AMI_MF","MCP73833T_AMI_MF:SON50P300X300X100-11N-D","1","MCP73833T-AMI/MF","Microchip Technology"
"IC102","MP2153GQFU-33-P","MP2153GQFU-33-P:MP2153GQFU-33-P","1","MP2153GQFU-33-P","Monolithic Power Systems"
"IC301,IC302,IC303,IC304","A3908EEETR-T","A3908EEETR-T:SON50P200X200X60-9N-D","4","A3908EEETR-T","Allegro MicroSystems"
"IC305","BMI323","BMI323:BMI323","1","BMI323","Bosch Sensortec"
"J101","2171780001","2171780001:MOLEX_2171780001","1","2171780001","Molex"
"J102","JST BATT","B2B_PH_K_S:JST_B2B-PH-K-S","1","B2B-PH-K-S","JST Sales America Inc."
"J201","UART","Connector_PinHeader_2.54mm:PinHeader_1x04_P2.54mm_Vertical","1","61300411121","Würth Elektronik"
"J309","SLW-108-01-G-S","SLW-108-01-G-S:SLW-108-01-G-S","1","SLW-108-01-G-S","Samtec"
"J310","SM04B-SRSS-TB_LF__SN_","SM04B-SRSS-TB_LF__SN_:JST_SM04B-SRSS-TB_LF__SN_","1","SM04B-SRSS-TB(LF)(SN)","JST Sales America Inc."
"L101","1uH","74437324010:WE-LHMI_4020","1","74437324010","Würth Elektronik"
"R101,R102","5k1","Resistor_SMD:R_0603_1608Metric","2","ERJ-3EKF5101V","Panasonic Electronic Components"
"R103,R104,R108","150","Resistor_SMD:R_0603_1608Metric","3","RC0603FR-07150RL","YAGEO"
"R105,R106","1k3","Resistor_SMD:R_0603_1608Metric","2","ERA-3AEB132V","Panasonic Electronic Components"
"R107","75k","Resistor_SMD:R_0603_1608Metric","1","ERJ-PB3B7502V","Panasonic Electronic Components"
"R109,R110","100k","Resistor_SMD:R_0603_1608Metric","2","ERJ-3EKF1003V","Panasonic Electronic Components"
"R201,R202,R207,R208,R209,R210,R213,R302,R304,R306,R308","10k","Resistor_SMD:R_0603_1608Metric","11","RC1608F103CS","Samsung Electro-Mechanics"
"R203,R204,R205,R206","100","Resistor_SMD:R_0603_1608Metric","4","RC0603FR-07100RL","YAGEO"
"R211,R212","2k2","Resistor_SMD:R_0603_1608Metric","2","RC1608F222CS","Samsung Electro-Mechanics"
"R301,R303,R305,R307","7k5","Resistor_SMD:R_0603_1608Metric","4","AT0603BRD077K5L","YAGEO"
"S101","500SSP1S1M2QEA","500SSP1S1M2QEA:500SSP1S1M2QEA","1","500SSP1S1M2QEA","E-Switch"
"S201,S202","PTS810SJK250SMTR_LFS","PTS810SJK250SMTR_LFS:PTS810SJK250SMTRLFS","2","PTS810SJK250SMTR LFS","C&K"
"TH101","10k","Resistor_SMD:R_0603_1608Metric","1","NTCG163JF103HT1","TDK Corporation"
"U201","ESP32-S3-MINI-1","RF_Module:ESP32-S2-MINI-1","1","ESP32-S3-MINI-1-N8","Espressif Systems"
